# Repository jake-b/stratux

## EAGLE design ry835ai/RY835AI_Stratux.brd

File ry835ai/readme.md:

Disclaimer
==========

BECAUSE THE HARDWARE DESIGN IS LICENSED FREE OF CHARGE, THERE IS NO WARRANTY
FOR THE HARDWARE DESIGN, TO THE EXTENT PERMITTED BY APPLICABLE LAW. EXCEPT 
WHEN OTHERWISE STATED IN WRITING THE COPYRIGHT HOLDERS AND/OR OTHER PARTIES 
PROVIDE THE HARDWARE DESIGN "AS IS" WITHOUT WARRANTY OF ANY KIND, EITHER 
EXPRESSED OR IMPLIED, INCLUDING, BUT NOT LIMITED TO, THE IMPLIED WARRANTIES 
OF MERCHANTABILITY AND FITNESS FOR A PARTICULAR PURPOSE. THE ENTIRE RISK AS 
TO THE QUALITY AND PERFORMANCE OF THE PROGRAM & HARDWARE DESIGN IS WITH YOU. 
SHOULD THE HARDWARE DESIGN PROVE DEFECTIVE, YOU ASSUME THE COST OF ALL 
NECESSARY SERVICING, REPAIR OR CORRECTION.

IN NO EVENT UNLESS REQUIRED BY APPLICABLE LAW OR AGREED TO IN WRITING WILL ANY 
COPYRIGHT HOLDER, OR ANY OTHER PARTY WHO MAY MODIFY AND/OR REDISTRIBUTE THE 
HARDWARE DESIGN AS PERMITTED ABOVE, BE LIABLE TO YOU FOR DAMAGES, INCLUDING 
ANY GENERAL, SPECIAL, INCIDENTAL OR CONSEQUENTIAL DAMAGES ARISING OUT OF THE 
USE OR INABILITY TO USE THE PROGRAM OR HARDWARE DESIGN (INCLUDING BUT NOT 
LIMITED TO LOSS OF DATA OR DATA BEING RENDERED INACCURATE OR LOSSES SUSTAINED 
BY YOU OR THIRD PARTIES OR A FAILURE OF THE PROGRAM OR HARDWARE DESIGN TO 
OPERATE WITH ANY OTHER PROGRAMS OR HARDWARE), EVEN IF SUCH HOLDER OR OTHER 
PARTY HAS BEEN ADVISED OF THE POSSIBILITY OF SUCH DAMAGES.

RA835AI Rasberry Pi "HAT" for Stratux 
=====================================

This board is designed for DEVELOPMENT PURPOSES ONLY.  It is not intended for
use in flight or in an airplane.  Use this board at your own risk!

This is a really rough draft of a "HAT" (Hardware Attached on Top) to connect
a RA835AI to the Rasberry Pi for use primarily with Stratux.

Currently it is just  a starting point.  Some things yet to work out:

- Is FSYNC supposed to be grounded?  Data sheet says yes; forums leave doubt.
- Pull-ups for I2C? - not necessary, as I understand that the Pi itself has
1.8k pullups

I tried by best to keep the ground planes clear of traces so that hopefully
it shields the GPS module from the Pi processor underneith.

This uses a custom library for the RA835AI, and a contributed library from
www.cadsoftusa.com "raspberrypi_bastelstube_v13" for the Pi GPIO connector
and board layout.

Revision History
================
- 0.1  - Initial commit
- 0.2  - Added C1 and C2 decoupling capacitors.  0.1uF  (P-tolerance=+100% ,-0%) 
         and 10uF values recommended by on the RY835AI data sheet. 
         Added a cut-trace jumper to disconnect FSYNC from GND if desired.
- 0.3  - Keepout area added underneith GPS antenna area.  Pads around mount
         points reduced and made round to make room for signal traces.
- 0.4  - Added "PWR IN" circut -- [see page 14](https://learn.adafruit.com/downloads/pdf/introducing-the-raspberry-pi-model-b-plus-plus-differences-vs-model-b.pdf)
         Added FAN output controlled by GPIO4.
         (minor change to explicitly list R1's value as 10k)
- 0.5  - Modified fan control signal to use GPIO18 rather than GPIO4.
         This is consistent with currently used AHRS boards.
         This revision has not been manufactured or tested, so make sure to 
         ERC/DRC and double check if you decide to have this made.

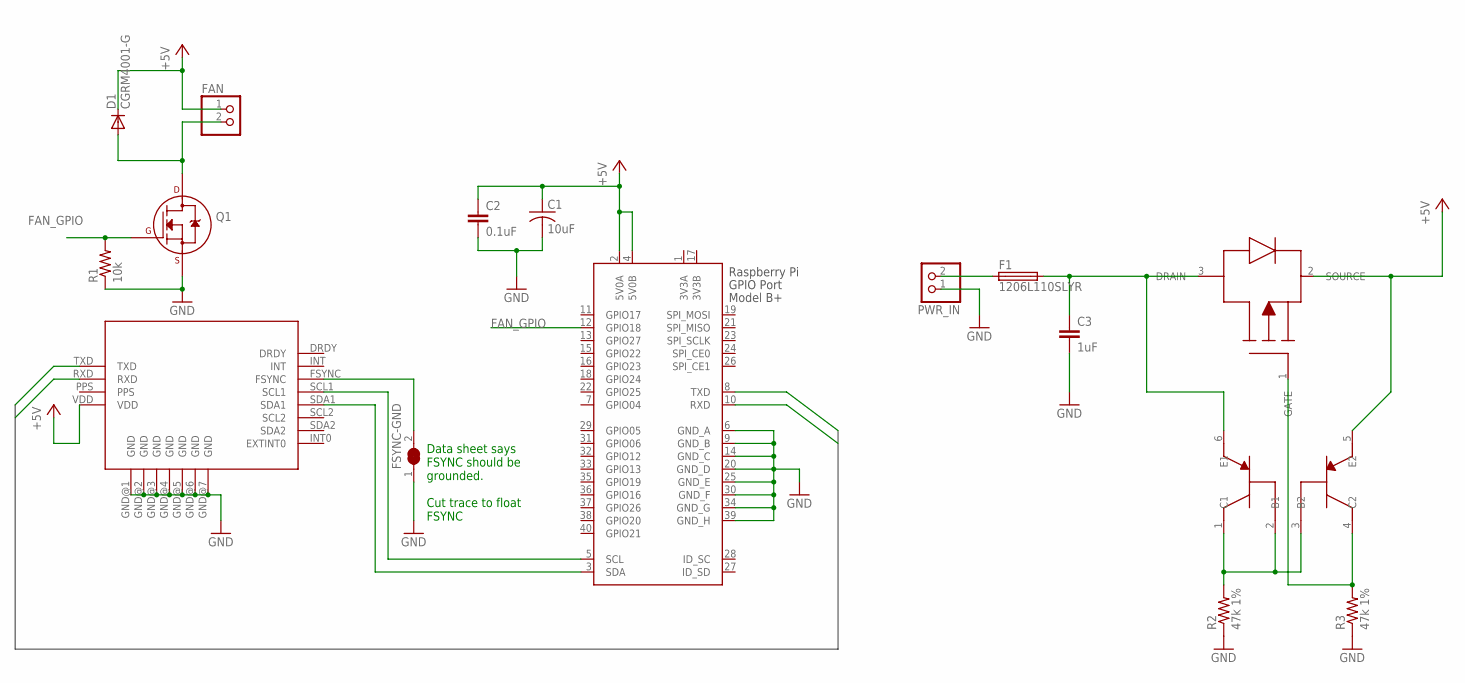
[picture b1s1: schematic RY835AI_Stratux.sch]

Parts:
C1: 10uF; C0805
C2: 0.1uF; C0805
C3: 1uF; C0805
D1: CGRM4001-G; SOD-123_MINI-SMA
F1: 1206L110SLYR; R1206
FAN: PINHD-1X2; 1X02
FSYNC-GND: CUTJUMPER; R1206-CUTJUMPER
PWR_IN: PINHD-1X2; 1X02
Q1: 2N7000_SOT23; SOT-23
R1: 10k; R0805
R2, R3: 47k 1%; R0805
U$1: RY835AI
U$2: DMG2305UX; SOT23
U$3: DMMT5401; SOT26
X2: RASPI_BOARD_B+#_HD; RASPI_BOARD_B+HAT_DF

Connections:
3V3A: X2.1 (3V3A)
3V3B: X2.17 (3V3B)
+5V: C1.1, C2.1, D1.C, FAN.1, U$1.VDD, U$2.2 (SOURCE), U$3.5 (E2), X2.2 (5V0A), X2.4 (5V0B)
FAN_GPIO: Q1.1 (G), R1.2, X2.12 (GPIO18)
GND: C1.2, C2.2, C3.2, FSYNC-GND.1, PWR_IN.1, Q1.2 (S), R1.1, R2.1, R3.1, U$1.GND@1 (GND), U$1.GND@2 (GND), U$1.GND@3 (GND), U$1.GND@4 (GND), U$1.GND@5 (GND), U$1.GND@6 (GND), U$1.GND@7 (GND), X2.6 (GND_A), X2.9 (GND_B), X2.14 (GND_C), X2.20 (GND_D), X2.25 (GND_E), X2.30 (GND_F), X2.34 (GND_G), X2.39 (GND_H)
unnamed: U$1.SDA1, X2.3 (SDA)
unnamed: U$1.SCL1, X2.5 (SCL)
unnamed: FSYNC-GND.2, U$1.FSYNC
unnamed: D1.A, FAN.2, Q1.3 (D)
unnamed: F1.1, PWR_IN.2
unnamed: C3.1, F1.2, U$2.3 (DRAIN), U$3.6 (E1)
unnamed: R2.2, U$3.1 (C1), U$3.2 (B1), U$3.3 (B2)
unnamed: R3.2, U$2.1 (GATE), U$3.4 (C2)
RXTX_BUS0: U$1.RXD, X2.8 (TXD)
RXTX_BUS1: U$1.TXD, X2.10 (RXD)

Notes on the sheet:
Data sheet says FSYNC should be grounded. Cut trace to float FSYNC

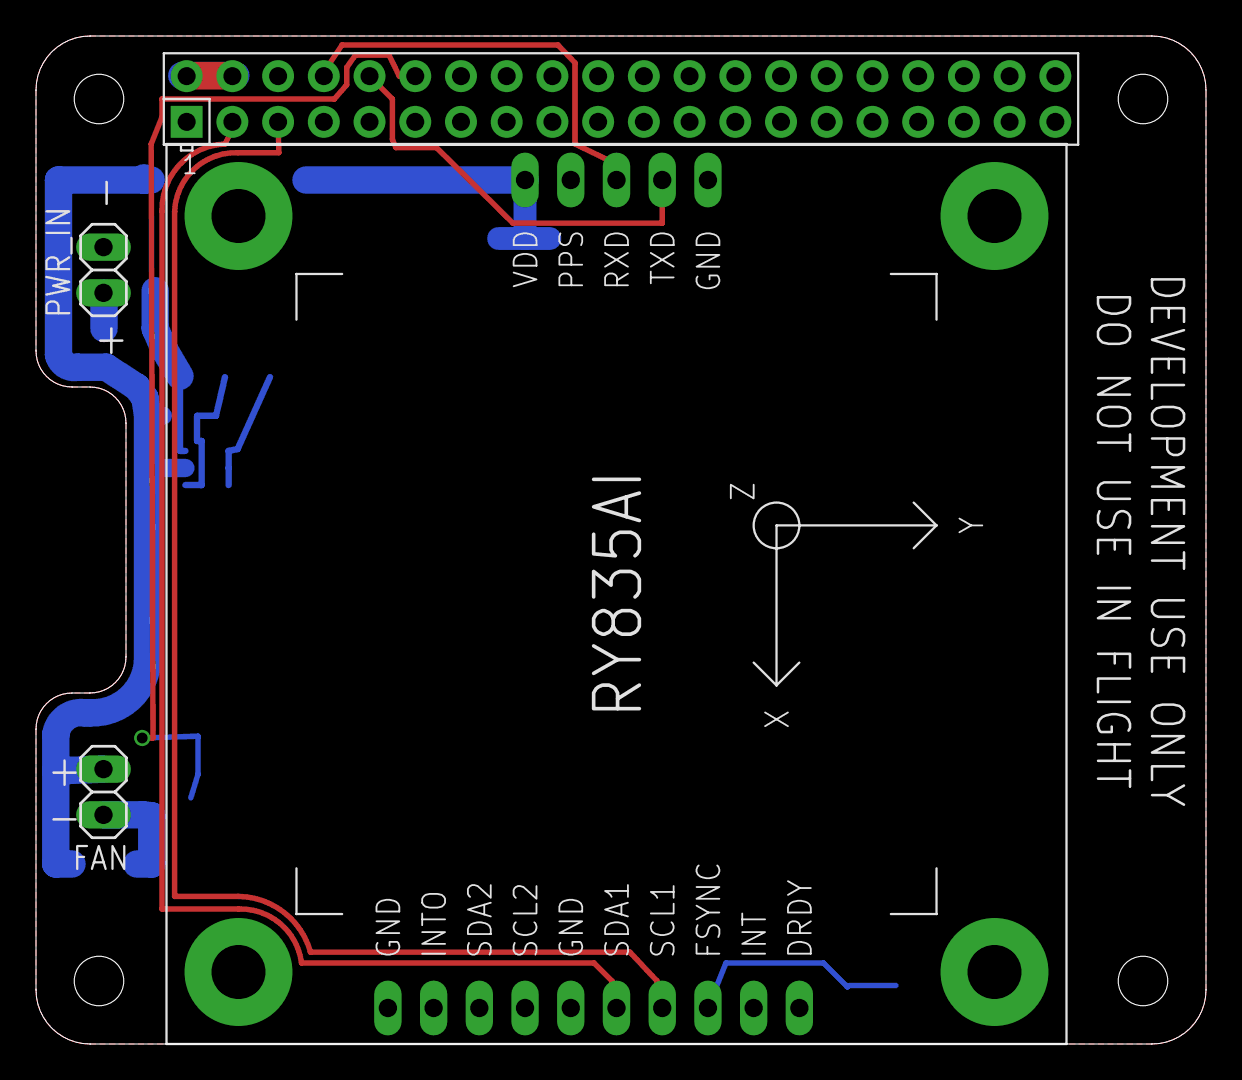
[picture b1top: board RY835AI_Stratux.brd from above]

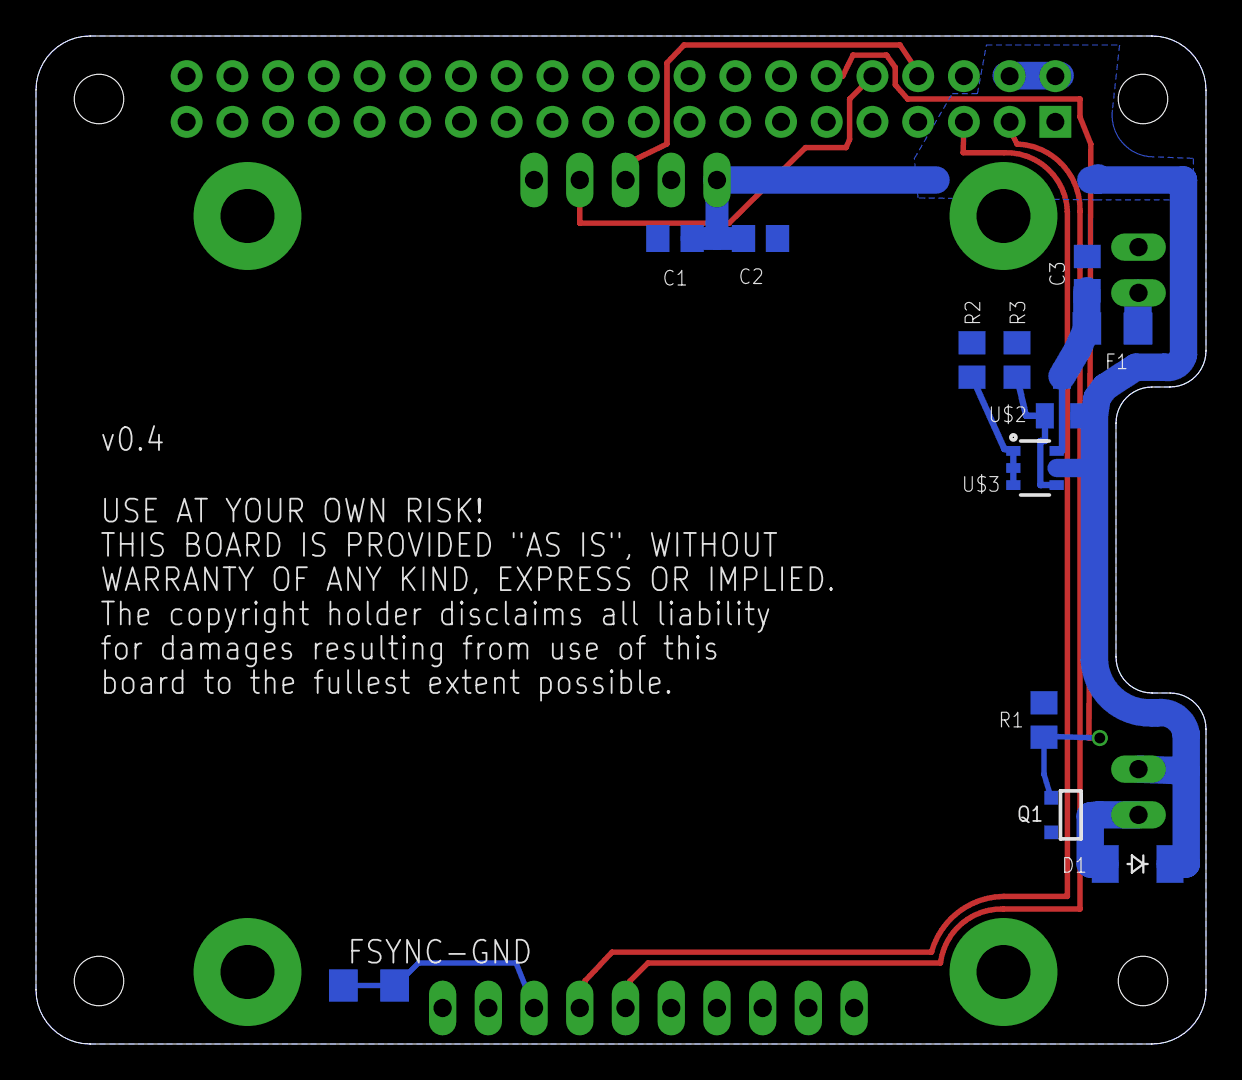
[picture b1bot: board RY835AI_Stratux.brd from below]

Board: 2 copper layers, 65.0 x 56.0 mm, 16 parts (12 on the bottom side), 13 nets.

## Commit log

2015-12-29 Initial commit of ry835ai draft hardware design.
2015-12-30 Added bypass caps and cut-jumper for FSYNC signal. Added image to readme.md
2016-01-01 Keepout area added underneith GPS antenna area. Pads around mount points redeuced and made round to make room for signal traces.
2016-01-02 added fan control
2016-01-28 Revised board design with provisions for FAN & PWR_IN.
2016-01-28 formatting
2016-01-29 Minor change R1=10k
2017-07-01 Modified fan control signal to use GPIO18 rather than GPIO4. This is consistent with currently used AHRS boards. This revision has not been manufactured or tested, so make sure to DRC and double chec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
